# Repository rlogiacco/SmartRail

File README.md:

SmartRail
=========

Arduino controlled modular camera rail system

Dependencies
---------

This firmware depends on the following open source libraries:

1. [VoltageReference](https://github.com/rlogiacco/VoltageReference)
2. [ArduinoDebug](https://github.com/rlogiacco/ArduinoDebug)
3. [AccelStepper](http://www.airspayce.com/mikem/arduino/AccelStepper/)
4. LiquidCrystal available among the standard Arduino libraries

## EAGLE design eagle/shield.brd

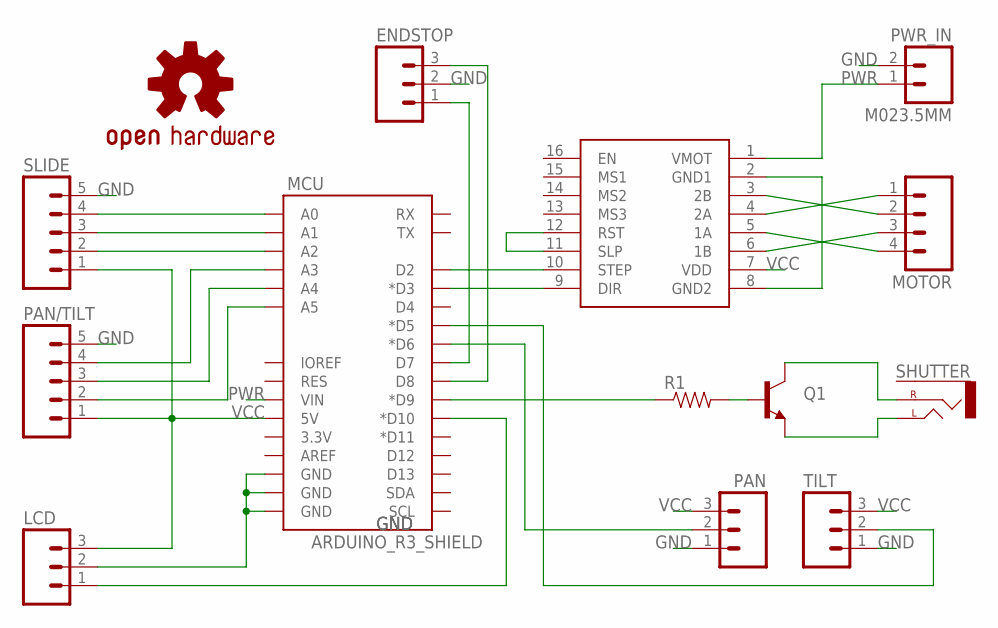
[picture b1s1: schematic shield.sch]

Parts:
ENDSTOP: M03PTH; 1X03
LCD: M03PTH; 1X03
LOGO1: OSHW-LOGOM; OSHW-LOGO-M
MCU: ARDUINO_R3_SHIELD; UNO_R3_SHIELD
MOTOR: M04POLAR; MOLEX-1X4
PAN: M03PTH; 1X03
PAN/TILT: M05PTH; 1X05
PWR_IN: M023.5MM; SCREWTERMINAL-3.5MM-2
Q1: TRANSISTOR_NPN2N3904; TO-92
R1: RESISTORAXIAL-0.3; AXIAL-0.3
SHUTTER: AUDIO-JACKPTH; AUDIO-JACK
SLIDE: M05PTH; 1X05
SOCKET: POLOLU DRIVER; DIL16
TILT: M03PTH; 1X03

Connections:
1A: MOTOR.4, SOCKET.5 (1A)
1B: MOTOR.3, SOCKET.6 (1B)
2A: MOTOR.1, SOCKET.4 (2A)
2B: MOTOR.2, SOCKET.3 (2B)
GND: ENDSTOP.2, LCD.2, MCU.GND@0 (GND), MCU.GND@1 (GND), MCU.GND@2 (GND), PAN.1, PAN/TILT.5, PWR_IN.2, SLIDE.5, TILT.1
unnamed: MCU.D2, SOCKET.10 (STEP)
unnamed: MCU.D3 (*D3), SOCKET.9 (DIR)
unnamed: LCD.1, MCU.D10 (*D10)
unnamed: MCU.A0, SLIDE.4
unnamed: MCU.A1, SLIDE.3
unnamed: MCU.A2, SLIDE.2
unnamed: MCU.D9 (*D9), R1.P$1 (1)
unnamed: Q1.2 (B), R1.P$2 (2)
unnamed: Q1.3 (C), SHUTTER.RING (RIGHT)
unnamed: Q1.1 (E), SHUTTER.TIP (LEFT)
unnamed: MCU.D6 (*D6), PAN.2
unnamed: ENDSTOP.1, MCU.D7
unnamed: ENDSTOP.3, MCU.D8
unnamed: MCU.D5 (*D5), TILT.2
unnamed: SOCKET.2 (GND1), SOCKET.8 (GND2)
unnamed: MCU.A3, PAN/TILT.4
unnamed: MCU.A4, PAN/TILT.3
unnamed: MCU.A5, PAN/TILT.2
unnamed: SOCKET.11 (SLP), SOCKET.12 (RST)
PWR: MCU.VIN, PWR_IN.1, SOCKET.1 (VMOT)
VCC: LCD.3, MCU.5V, PAN.3, PAN/TILT.1, SLIDE.1, SOCKET.7 (VDD), TILT.3

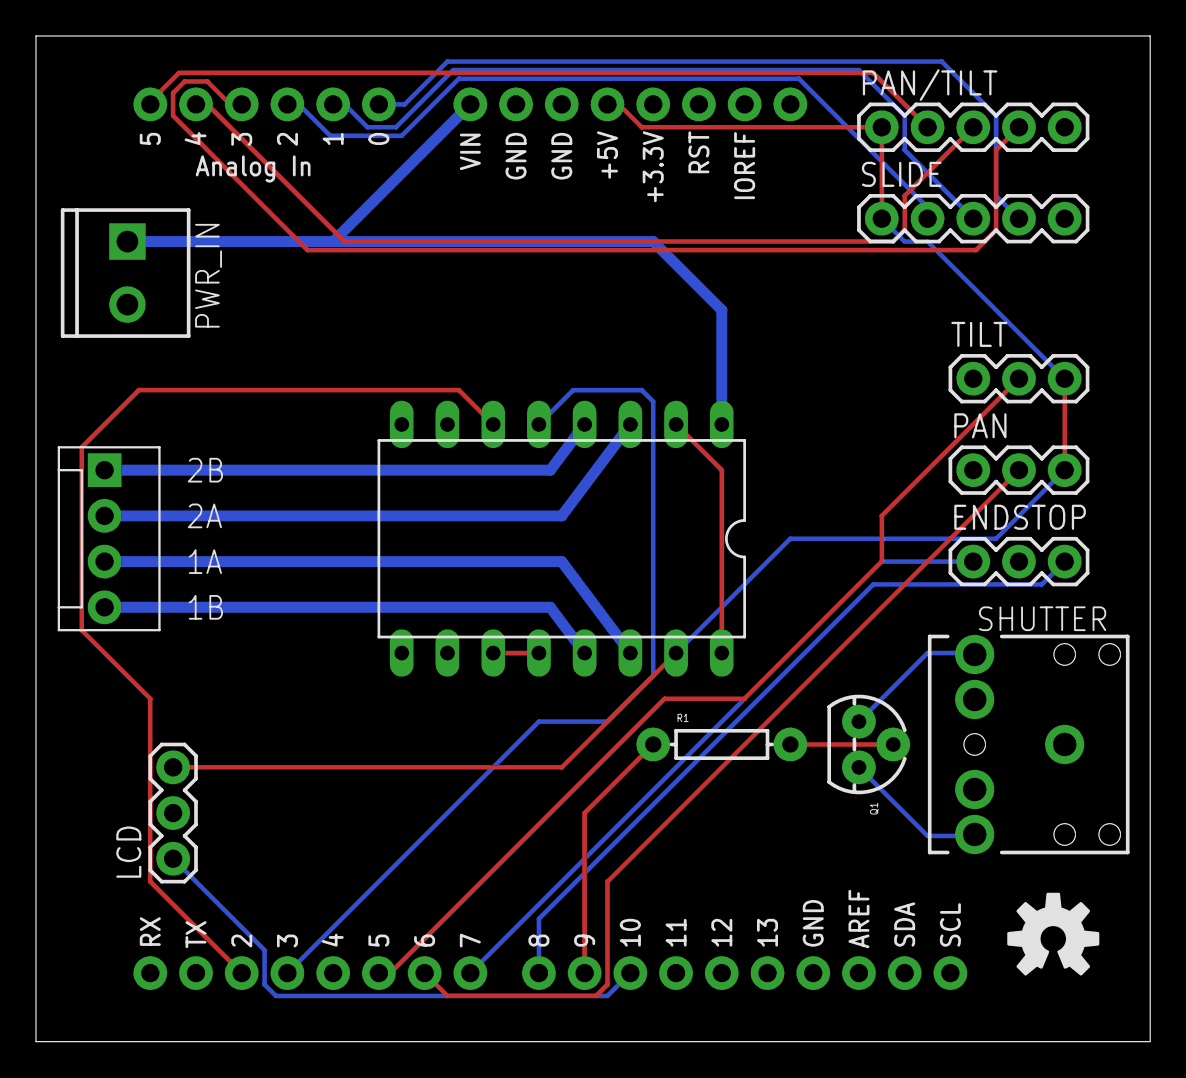
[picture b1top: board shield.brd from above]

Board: 2 copper layers, 61.9 x 55.9 mm, 14 parts (0 on the bottom side), 26 nets.

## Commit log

2014-07-15 starting up
2014-07-16 init oop implementation
2014-07-16 added stepper demo
2014-07-17 updated joystick
2014-07-19 added localization support
2014-07-19 implemented manual mode, constant speed and smoothed stepper demo
2014-07-19 improved joystick implementation
2014-07-19 fixed implementation
2014-07-19 reactivated functions
2014-07-19 clean up
2014-07-23 added symbols
2014-07-23 added debounce and board schematics
2014-07-23 added menu mindmap
2014-07-23 added dependencies list
2014-07-23 removed unused dependency
2014-07-23 deleted local dependencies copy
2014-11-24 added Eagle files
2014-11-24 updated shield schematics to include a second joystick and two servos to control pan and tilt
2014-11-24 refined board design
2015-08-08 switched to .ino file

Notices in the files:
parts and their libraries:
SparkFun-Connectors: Licensing: Creative Commons ShareAlike 4.0 International - https://creativecommons.org/licenses/by-sa/4.0
